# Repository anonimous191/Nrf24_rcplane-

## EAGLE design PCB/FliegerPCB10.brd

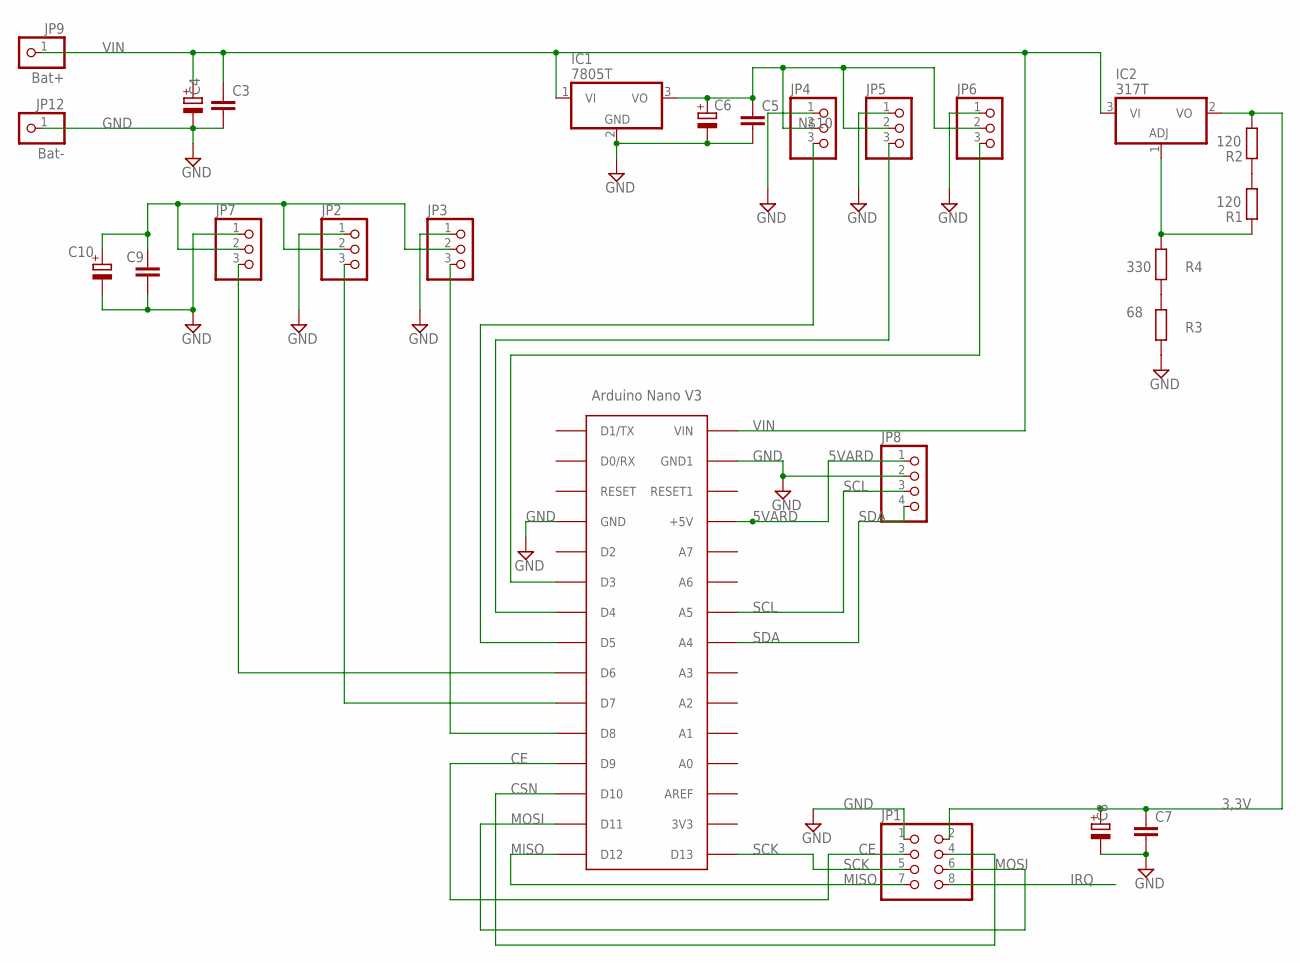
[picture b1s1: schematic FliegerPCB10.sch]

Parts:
C3, C5, C7, C9: C-EU050-024X044; C050-024X044
C4, C6, C10: CPOL-EUE5-10.5; E5-10,5
C8: CPOL-EUE3.5-8; E3,5-8
IC1: 7805T; TO220H
IC2: 317T; TO220H
JP1: PINHD-2X4; 2X04
JP2, JP3, JP4, JP5, JP6, JP7: PINHD-1X3; 1X03
JP8: PINHD-1X4; 1X04
JP9: Bat+; 1X01
JP12: Bat-; 1X01
R1, R2: 120; 0207/10
R3: 68; 0207/10
R4: 330; 0207/10
U$1: ARDUINONANO; PDIP-32

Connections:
3,3V: C7.1, C8.+, IC2.2 (VO), JP1.2, R2.2
5VARD: JP8.1, U$1.+5V
CE: JP1.3, U$1.D9
CSN: JP1.4, U$1.D10
GND: C3.2, C4.-, C5.2, C6.-, C7.2, C8.-, C9.2, C10.-, IC1.2 (GND), JP1.1, JP2.1, JP3.1, JP4.1, JP5.1, JP6.1, JP7.1, JP8.2, JP12.1, R3.2, U$1.GND, U$1.GND1
IRQ: JP1.8
MISO: JP1.7, U$1.D12
MOSI: JP1.6, U$1.D11
unnamed: JP7.3, U$1.D6
unnamed: JP2.3, U$1.D7
unnamed: JP3.3, U$1.D8
unnamed: JP4.3, U$1.D5
unnamed: JP5.3, U$1.D4
unnamed: JP6.3, U$1.D3
unnamed: R1.2, R2.1
unnamed: IC2.1 (ADJ), R1.1, R4.1
unnamed: R3.1, R4.2
unnamed: C5.1, C6.+, IC1.3 (VO), JP4.2, JP5.2, JP6.2
unnamed: C9.1, C10.+, JP2.2, JP3.2, JP7.2
SCK: JP1.5, U$1.D13
SCL: JP8.3, U$1.A2 (A5)
SDA: JP8.4, U$1.A3 (A4)
VIN: C3.1, C4.+, IC1.1 (VI), IC2.3 (VI), JP9.1, U$1.VIN

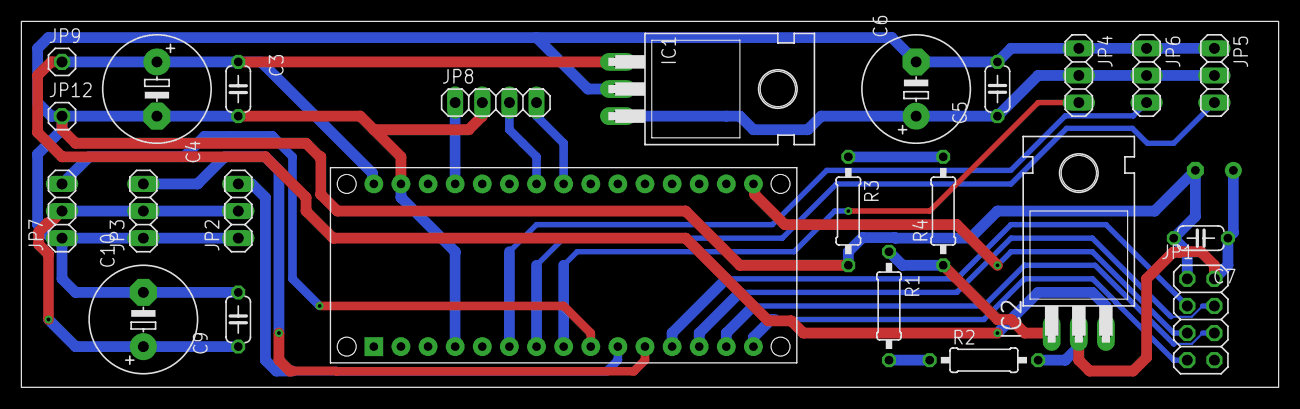
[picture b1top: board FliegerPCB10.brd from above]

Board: 2 copper layers, 117.8 x 34.3 mm, 25 parts (1 on the bottom side), 22 nets.

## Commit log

2025-02-04 Rc plane code versions
    these are the different rx and tx versions of my code and it should work with the basic spi pinout and ce being 9 and csn being 10 on the nrf24l01
2025-02-04 nrf24 lib, use 1.4.10!!!
    make sure to use the 1.4.10 version
2025-02-04 adafruit MPU6050 library
2025-02-04 PCb not printed yet
